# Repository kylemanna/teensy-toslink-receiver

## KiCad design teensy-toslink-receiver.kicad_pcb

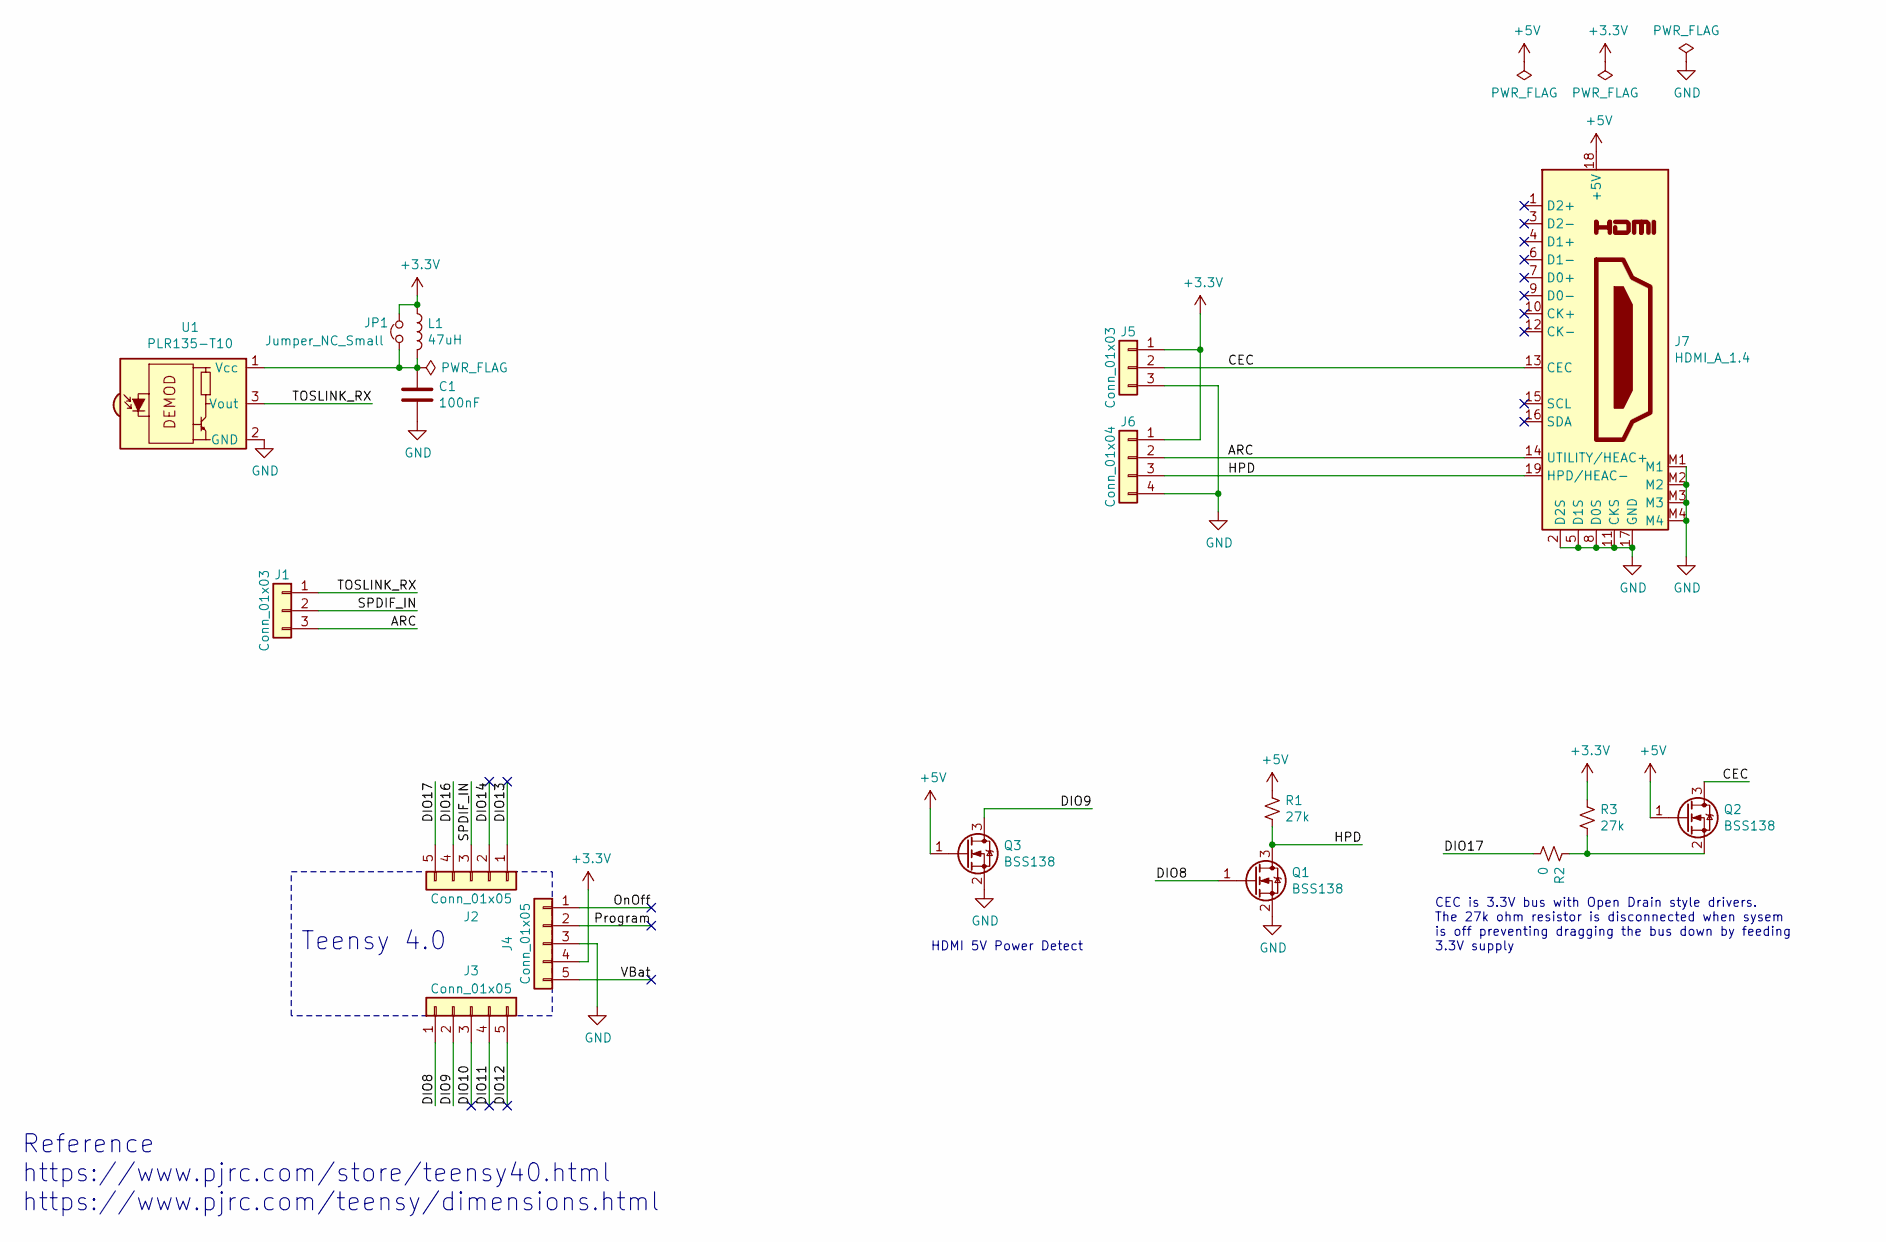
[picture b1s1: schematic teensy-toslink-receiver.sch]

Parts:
C1: 100nF; C_0603_1608Metric
J1, J5: Conn_01x03; PinHeader_1x03_P2.54mm_Vertical
J2, J3, J4: Conn_01x05; PinHeader_1x05_P2.54mm_Vertical
J6: Conn_01x04; PinHeader_1x04_P2.54mm_Vertical
J7: HDMI_A_1.4; Amphenol_ICC-10029449-001RLF-MFG
JP1: Jumper_NC_Small; SolderJumper-2_P1.3mm_Bridged_RoundedPad1.0x1.5mm
L1: 47uH; L_0805_2012Metric
Q1, Q2, Q3: BSS138; SOT-23
R1, R3: 27k; R_0201_0603Metric
R2: 0; R_0201_0603Metric
U1: PLR135-T10; Everlight_PLR135-T10

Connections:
+3V3: J4.4, J5.1, J6.1, JP1.2, L1.1, R3.2
+5V: J7.18 (+5V), Q2.1 (G), Q3.1 (G), R1.1
/ARC: J1.3, J6.2, J7.14 (UTILITY/HEAC+)
/CEC: J5.2, J7.13 (CEC), Q2.3 (D)
/DIO8: J3.1, Q1.1 (G)
/DIO9: J3.2, Q3.3 (D)
/DIO10: J3.3
/DIO11: J3.4
/DIO12: J3.5
/DIO13: J2.1
/DIO14: J2.2
/DIO16: J2.4
/DIO17: J2.5, R2.2
/HPD: J6.3, J7.19 (HPD/HEAC-), Q1.3 (D), R1.2
/OnOff: J4.1
/Program: J4.2
/SPDIF_IN: J1.2, J2.3
/TOSLINK_RX: J1.1, U1.3 (Vout)
/VBat: J4.5
GND: C1.2, J4.3, J5.3, J6.4, J7.2 (D2S), J7.5 (D1S), J7.8 (D0S), J7.11 (CKS), J7.17 (GND), J7.M1, J7.M2, J7.M3, J7.M4, Q1.2 (S), Q3.2 (S), U1.2 (GND)
unnamed: C1.1, JP1.1, L1.2, U1.1 (Vcc)
unnamed: Q2.2 (S), R2.1, R3.1

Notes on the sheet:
Reference https://www.pjrc.com/store/teensy40.html https://www.pjrc.com/teensy/dimensions.html
Teensy 4.0
CEC is 3.3V bus with Open Drain style drivers. The 27k ohm resistor is disconnected when sysem is off preventing dragging the bus down by feeding 3.3V supply
HDMI 5V Power Detect

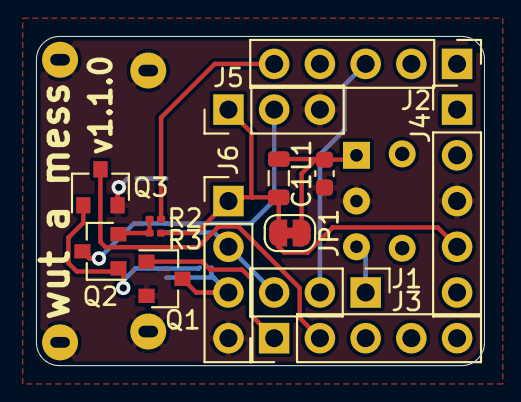
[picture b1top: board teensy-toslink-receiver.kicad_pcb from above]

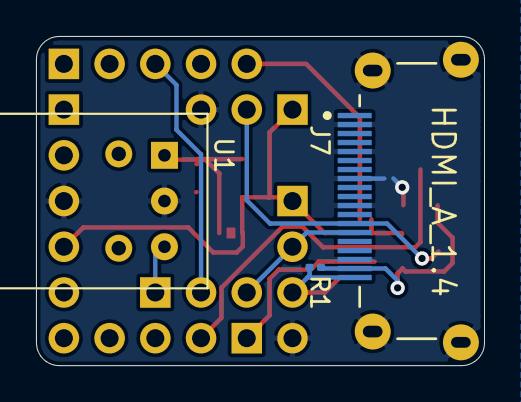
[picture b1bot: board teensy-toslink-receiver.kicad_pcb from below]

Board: 2 copper layers, 24.9 x 18.3 mm, 17 parts (3 on the bottom side), 13 nets.

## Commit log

2020-11-16 repo: Inital commit
2020-11-16 pcb: Add first pass at PCB
    * I think this works.
2020-11-16 gerbers: Add gerbers
    * Sent to OSHPark with zip timestamp 1605504464
    * $3.50 for 3x shipped.
2020-11-28 pcb: Tighten up footprints
    * Tighten up the holes for footprints after fitting OSH Park PCB.
2020-12-26 pcb: Fix incorrectly placed Teensy headers and move connectors to bottom
    * Headers were on inside when they should be on the outside. Oops.
    * HDMI and TOSLINK connectors moved to bottom to prevent blocking teensy
    reset button.
2020-12-26 schematic: Add HPD and CEC FETs
    * N-Channel MOSFET to pull HPD low on connection.
    * N-Channel MOSFET acting as a diode to prevent dragging bus down.
    * N-Channel MOSFET to detect when HDMI cable is plugged in and 5V is
    available to start operation.
2020-12-26 pcb: Update PCB with new components
    * Tighten up tolerances with OSH Park rules for 0603 components.
2020-12-26 gerbers: Update gerbers v1.1.0
    * Sent to OSHPark with zip timestamp 1608996768
    * $3.50 for 3x shipped.
